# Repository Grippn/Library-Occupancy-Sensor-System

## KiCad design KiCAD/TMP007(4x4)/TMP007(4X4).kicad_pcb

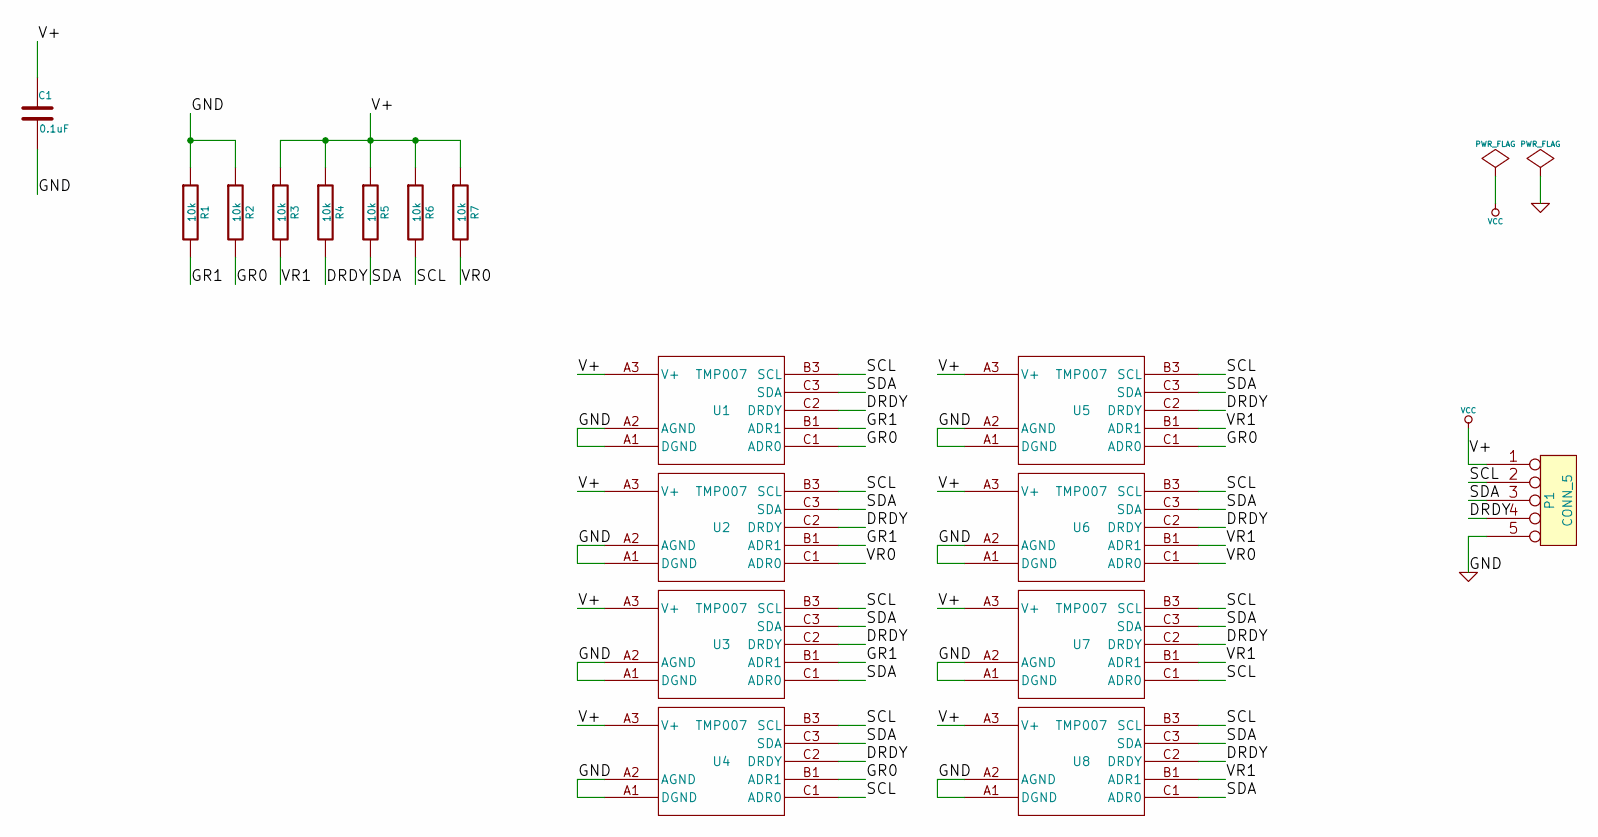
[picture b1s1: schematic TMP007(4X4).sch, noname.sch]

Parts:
C1: 0.1uF
P1: CONN_5
R1, R2, R3, R4, R5, R6, R7: 10k
U1, U2, U3, U4, U5, U6, U7, U8: TMP007

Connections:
/DRDY: P1.4, R4.2, U1.C2 (DRDY), U2.C2 (DRDY), U3.C2 (DRDY), U4.C2 (DRDY), U5.C2 (DRDY), U6.C2 (DRDY), U7.C2 (DRDY), U8.C2 (DRDY)
/GR0: R2.2, U1.C1 (ADR0), U4.B1 (ADR1), U5.C1 (ADR0)
/GR1: R1.2, U1.B1 (ADR1), U2.B1 (ADR1), U3.B1 (ADR1)
/SCL: P1.2, R6.2, U1.B3 (SCL), U2.B3 (SCL), U3.B3 (SCL), U4.B3 (SCL), U4.C1 (ADR0), U5.B3 (SCL), U6.B3 (SCL), U7.B3 (SCL), U7.C1 (ADR0), U8.B3 (SCL)
/SDA: P1.3, R5.2, U1.C3 (SDA), U2.C3 (SDA), U3.C1 (ADR0), U3.C3 (SDA), U4.C3 (SDA), U5.C3 (SDA), U6.C3 (SDA), U7.C3 (SDA), U8.C1 (ADR0), U8.C3 (SDA)
/VR0: R7.2, U2.C1 (ADR0), U6.C1 (ADR0)
/VR1: R3.2, U5.B1 (ADR1), U6.B1 (ADR1), U7.B1 (ADR1), U8.B1 (ADR1)
GND: C1.2, P1.5, R1.1, R2.1, U1.A1 (DGND), U1.A2 (AGND), U2.A1 (DGND), U2.A2 (AGND), U3.A1 (DGND), U3.A2 (AGND), U4.A1 (DGND), U4.A2 (AGND), U5.A1 (DGND), U5.A2 (AGND), U6.A1 (DGND), U6.A2 (AGND), U7.A1 (DGND), U7.A2 (AGND), U8.A1 (DGND), U8.A2 (AGND)
VCC: C1.1, P1.1, R3.1, R4.1, R5.1, R6.1, R7.1, U1.A3 (V+), U2.A3 (V+), U3.A3 (V+), U4.A3 (V+), U5.A3 (V+), U6.A3 (V+), U7.A3 (V+), U8.A3 (V+)

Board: 2 copper layers, 17 parts (0 on the bottom side), 9 nets, no tracks yet.

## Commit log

2015-04-10 Layout and Design Files for the TMP006 & TMP007
2015-04-19 Getting Traces Working
    Had re do the layout for the IR lens. Trying to get the routing and
    traces to work. There may be a problem with the paste layer on the top
    layer copper.
